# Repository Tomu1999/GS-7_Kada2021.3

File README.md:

# GS-7_Kada2021.3

2020年度3月加太共同実験
\nGS-7

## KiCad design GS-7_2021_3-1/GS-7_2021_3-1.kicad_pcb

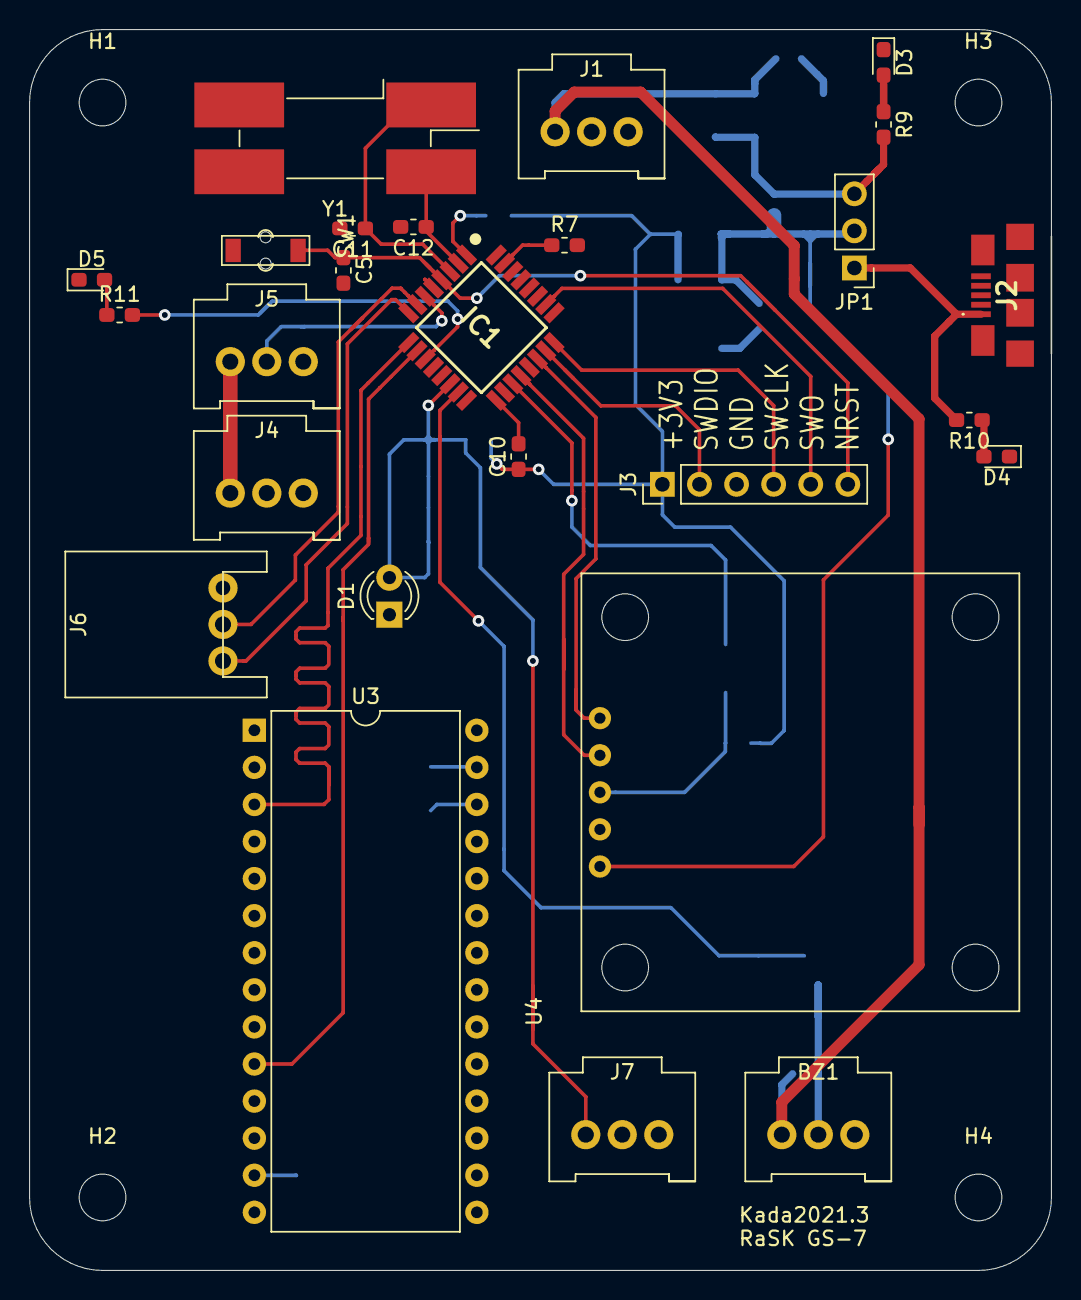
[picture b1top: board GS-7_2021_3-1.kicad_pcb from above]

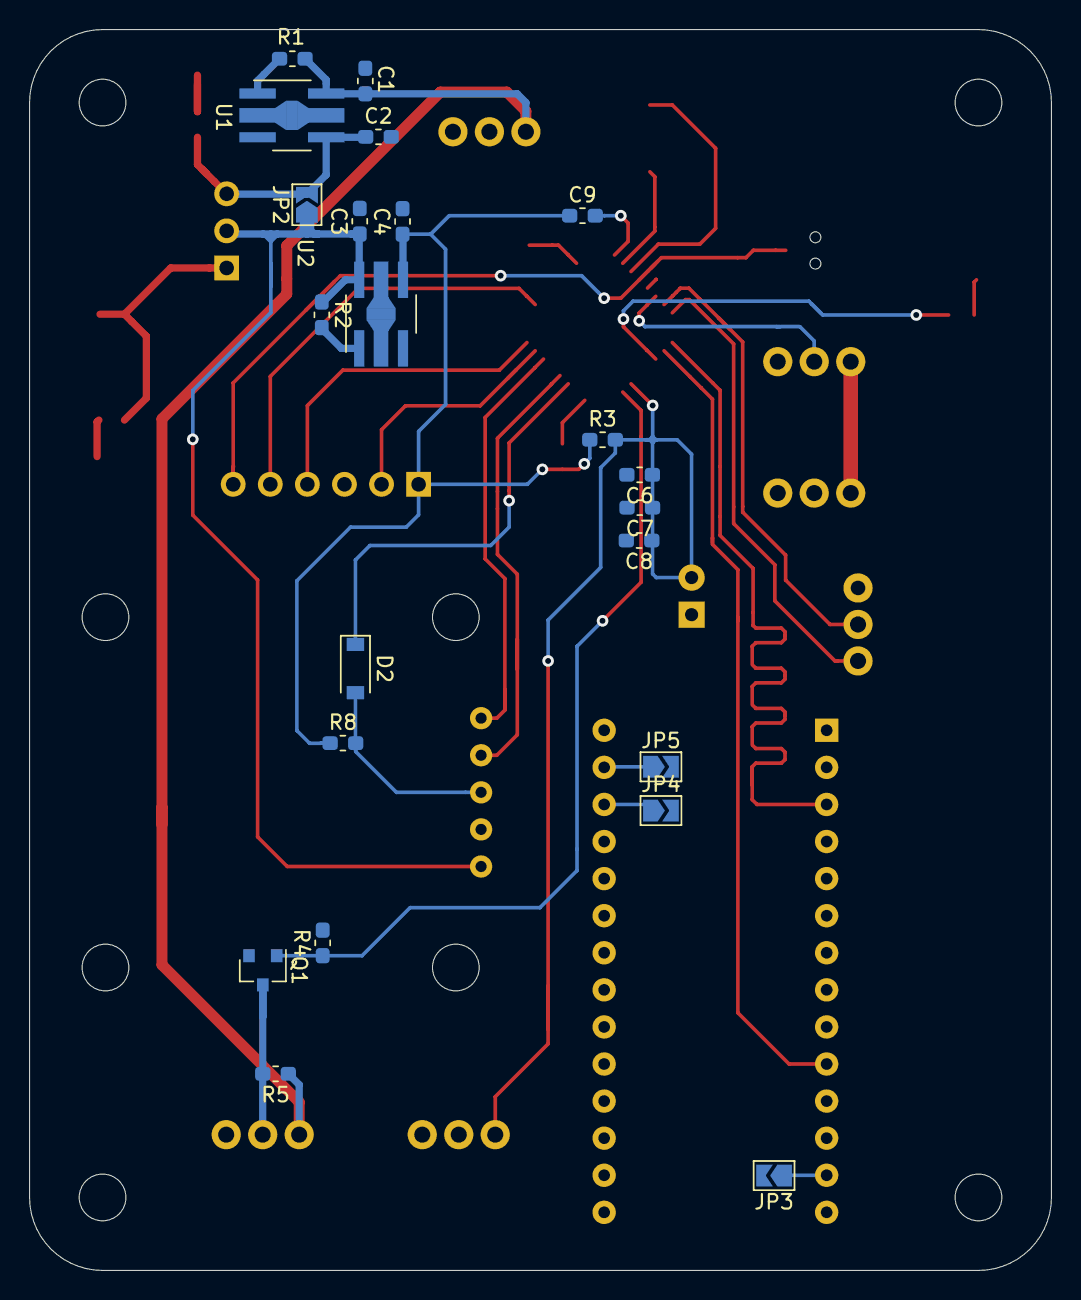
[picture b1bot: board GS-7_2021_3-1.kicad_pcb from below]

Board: 2 copper layers, 70.0 x 85.0 mm, 52 parts (22 on the bottom side), 37 nets.

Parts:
BZ1: Buzzer; Hirose_DF1E_DF1E-3P-2.5DS_1x03_P2.5mm_Vertical
C1, C3: 0.33μf; C_0603_1608Metric_Pad1.05x0.95mm_HandSolder
C2, C4: 2.2μf; C_0603_1608Metric_Pad1.05x0.95mm_HandSolder
C5, C6, C9, C10: 0.1μf; C_0603_1608Metric_Pad1.05x0.95mm_HandSolder
C7: 1μf; C_0603_1608Metric_Pad1.05x0.95mm_HandSolder
C8: 10μf; C_0603_1608Metric_Pad1.05x0.95mm_HandSolder
C11, C12: 12pf; C_0603_1608Metric_Pad1.05x0.95mm_HandSolder
D1: LED_Small; LED_D3.0mm
D2: 1N4148; D_SOD-123
D3, D4, D5: LED_Small; LED_0603_1608Metric_Pad1.05x0.95mm_HandSolder
H1, H2, H3, H4: MountingHole; MountingHole_3.2mm_M3
IC1: STM32F303K8T6; QFP80P900X900X160-32N
J1: 9V; Hirose_DF1E_DF1E-3P-2.5DS_1x03_P2.5mm_Vertical
J2: ZX62-B-5PA_33_; ZX62B5PA33
J3: ST-LINK/V2-1; PinHeader_1x06_P2.54mm_Vertical
J4: 6V; Hirose_DF1E_DF1E-3P-2.5DS_1x03_P2.5mm_Vertical
J5: Motor; Hirose_DF1E_DF1E-3P-2.5DS_1x03_P2.5mm_Vertical
J6: communication; Hirose_DF1E_DF1E-3P-2.5DS_1x03_P2.5mm_Horizontal
J7: Flight Pin; Hirose_DF1E_DF1E-3P-2.5DS_1x03_P2.5mm_Vertical
JP1: Jumper_3_Open; PinHeader_1x03_P2.54mm_Vertical
JP2: SB1; SolderJumper-2_P1.3mm_Open_TrianglePad1.0x1.5mm
JP3: SB2; SolderJumper-2_P1.3mm_Open_TrianglePad1.0x1.5mm
JP4: SB3; SolderJumper-2_P1.3mm_Open_TrianglePad1.0x1.5mm
JP5: SB4; SolderJumper-2_P1.3mm_Open_TrianglePad1.0x1.5mm
Q1: 2N7002K; SOT-23
R1, R2: R; R_0603_1608Metric_Pad1.05x0.95mm_HandSolder
R3, R4, R5, R9, R10, R11: 1k; R_0603_1608Metric_Pad1.05x0.95mm_HandSolder
R7, R8: 10k; R_0603_1608Metric_Pad1.05x0.95mm_HandSolder
SW1: SW_RESET; TVAF06-A020B-R
U1: NJM2884U1-05; SOT-89-5_Handsoldering
U2: NJM2884U1-33; SOT-89-5_Handsoldering
U3: MW-R-DP-W; DIP-28_W15.24mm
U4: GYSFDMAXB; AE-GYSFDMAXB
Y1: 8MHz; Crystal_SMD_SeikoEpson_MA506-4Pin_12.7x5.1mm_HandSoldering

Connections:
1pps: IC1.22, U4.5
+3V3: C4.1, C9.1, C10.1, J3.1, R3.1, R8.1, U2.4, U3.28
+5V: C3.1, JP1.2, JP2.1, R2.1, U2.5, U4.1
+6V: J4.1, J5.1
+9V: BZ1.1, C1.1, J1.1, R1.1, R5.1, U1.5
BATT_5V: C2.1, JP1.3, JP2.2, R9.2, U1.4
BOOT0: IC1.31, R7.1
Buzzer: IC1.15, Q1.1, R4.1
FPIN: C6.1, C7.1, C8.1, D1.2, IC1.14, J7.1, R3.2
FPIN_com: IC1.8, J6.1
GND: C1.2, C2.2, C3.2, C4.2, C5.2, C6.2, C7.2, C8.2, C11.2, C12.2, D1.1, D3.1, D4.1, D5.1, IC1.16, IC1.32, J1.2, J2.5, J2.MP1, J2.MP2, J2.MP3, J2.MP4, J2.MP5, J2.MP6, J3.3, J4.2, J5.3, J6.3, J7.2, JP3.2, JP4.2, JP5.2, Q1.2, R4.2, R7.2, SW1.2, U1.2, U2.2, U3.1, U3.14, U3.22, U3.24, U4.2
LED1: IC1.11, R11.2
Motor: IC1.6, J5.2
NRST: C5.1, IC1.4, J3.6, SW1.1
unnamed: BZ1.2, Q1.3, R5.2
unnamed: C9.2, IC1.1
unnamed: C10.2, IC1.17
unnamed: D2.2, R8.2, U4.3
unnamed: D3.2, R9.1
unnamed: D4.2, R10.1
unnamed: D5.2, R11.1
unnamed: JP3.1, U3.13
unnamed: JP4.1, U3.26
unnamed: JP5.1, U3.27
unnamed: R1.2, U1.1
unnamed: R2.2, U2.1
OSC_IN: C12.1, IC1.2, Y1.4
OSC_OUT: C11.1, IC1.3, Y1.1
SIG: IC1.7, J6.2
SWCLK: IC1.24, J3.4
SWDIO: IC1.23, J3.2
SWO: IC1.26, J3.5
UART1_RX: IC1.20, U4.4
UART1_TX: D2.1, IC1.19
UART2_RX: IC1.10, U3.10
UART2_TX: IC1.9, U3.3
USB_5V: J2.1, JP1.1, R10.2
